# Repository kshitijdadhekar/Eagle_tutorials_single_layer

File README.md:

# Eagle_tutorials
The video tutorials can be found on <a href="https://www.youtube.com/watch?v=hYVQ5IdzsRg&list=PLr0mEvO7yBe6QHexsgU2WFUGesFFobGZp">Terminal Two's YouTube channel</a><br>

This repository contains the following:
1. Eagle schematic file
2. Eagle board file
3. BOM
4. Gerbers
5. PDFs of the schematic and the board files

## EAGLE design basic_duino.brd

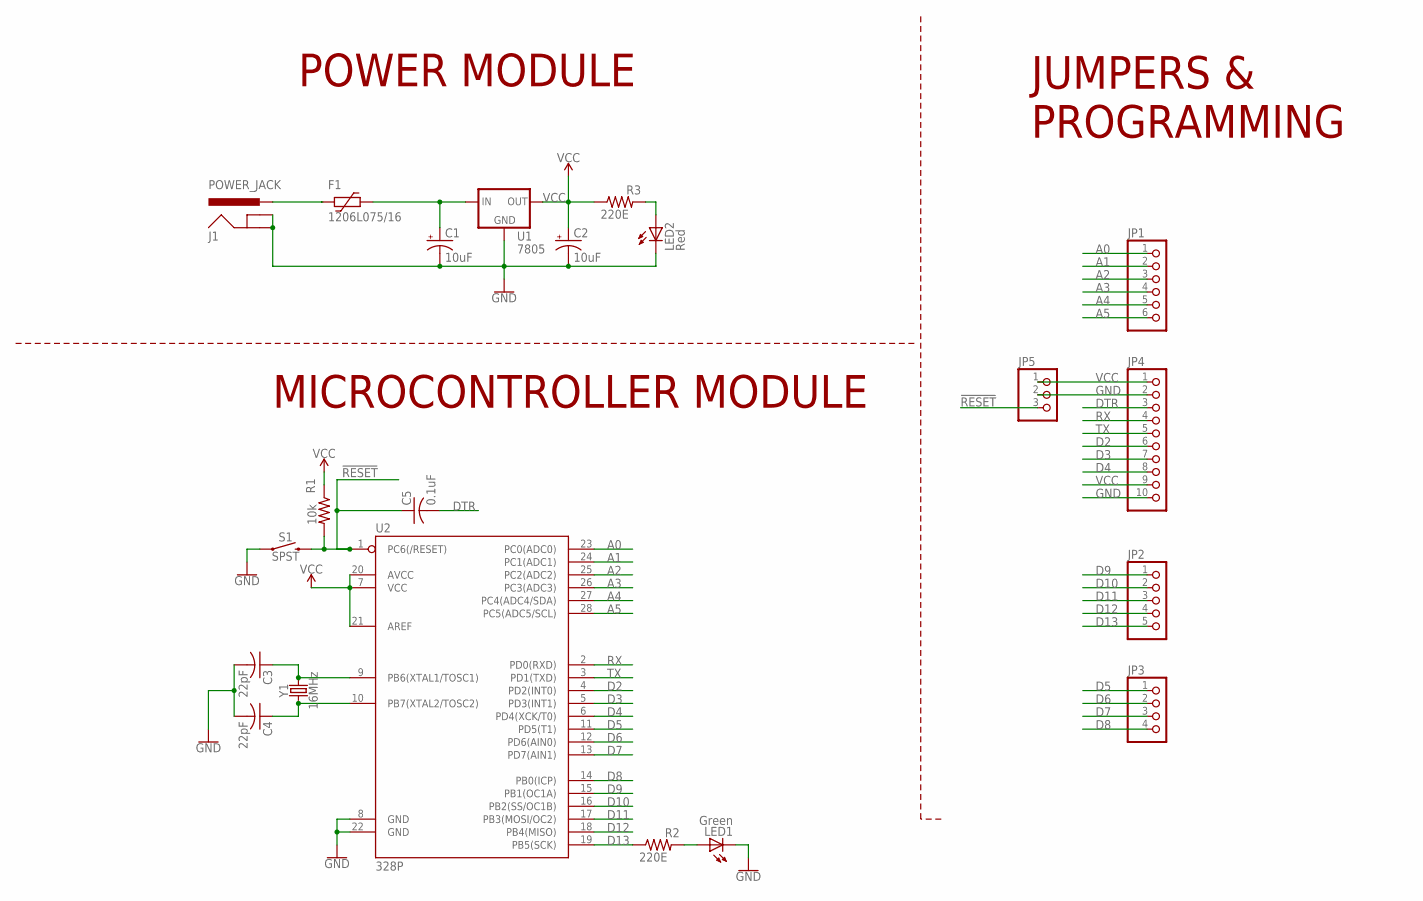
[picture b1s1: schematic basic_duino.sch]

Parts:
C1, C2: 10uF; E2,5-6
C3, C4: 22pF; C025-025X050
C5: 0.1uF; C025-025X050
F1: 1206L075/16; 1206L
J1: POWER_JACK; POWER_JACK_PTH
JP1: PINHD-1X6; 1X06
JP2: PINHD-1X5; 1X05
JP3: PINHD-1X4; 1X04
JP4: PINHD-1X10; 1X10
JP5: PINHD-1X3; 1X03
LED1: Green; LED3MM
LED2: Red; LED3MM
R1: 10k; 0204/7
R2, R3: 220E; 0204/7
S1: SPST; TACTILE_SWITCH_PTH_6.0MM
U1: 7805; 78XXS
U2: 328P; DIP28
Y1: 16MHz; HC49US

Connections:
!RESET: C5.1, JP5.3, R1.2, S1.3 (2), U2.1 (PC6(/RESET))
A0: JP1.1, U2.23 (PC0(ADC0))
A1: JP1.2, U2.24 (PC1(ADC1))
A2: JP1.3, U2.25 (PC2(ADC2))
A3: JP1.4, U2.26 (PC3(ADC3))
A4: JP1.5, U2.27 (PC4(ADC4/SDA))
A5: JP1.6, U2.28 (PC5(ADC5/SCL))
D2: JP4.6, U2.4 (PD2(INT0))
D3: JP4.7, U2.5 (PD3(INT1))
D4: JP4.8, U2.6 (PD4(XCK/T0))
D5: JP3.1, U2.11 (PD5(T1))
D6: JP3.2, U2.12 (PD6(AIN0))
D7: JP3.3, U2.13 (PD7(AIN1))
D8: JP3.4, U2.14 (PB0(ICP))
D9: JP2.1, U2.15 (PB1(OC1A))
D10: JP2.2, U2.16 (PB2(SS/OC1B))
D11: JP2.3, U2.17 (PB3(MOSI/OC2))
D12: JP2.4, U2.18 (PB4(MISO))
D13: JP2.5, R2.1, U2.19 (PB5(SCK))
DTR: C5.2, JP4.3
GND: C1.-, C2.-, C3.2, C4.2, J1.GND, J1.GNDBREAK, JP4.2, JP4.10, JP5.2, LED1.K (C), LED2.K (C), S1.1, U1.GND, U2.8 (GND), U2.22 (GND)
unnamed: C1.+, F1.1, U1.IN
unnamed: C3.1, U2.9 (PB6(XTAL1/TOSC1)), Y1.2
unnamed: C4.1, U2.10 (PB7(XTAL2/TOSC2)), Y1.1
unnamed: LED2.A, R3.2
unnamed: LED1.A, R2.2
unnamed: F1.2, J1.PWR
RX: JP4.4, U2.2 (PD0(RXD))
TX: JP4.5, U2.3 (PD1(TXD))
VCC: C2.+, JP4.1, JP4.9, JP5.1, R1.1, R3.1, U1.OUT, U2.7 (VCC), U2.20 (AVCC), U2.21 (AREF)

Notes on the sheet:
JUMPERS & PROGRAMMING
POWER MODULE
MICROCONTROLLER MODULE

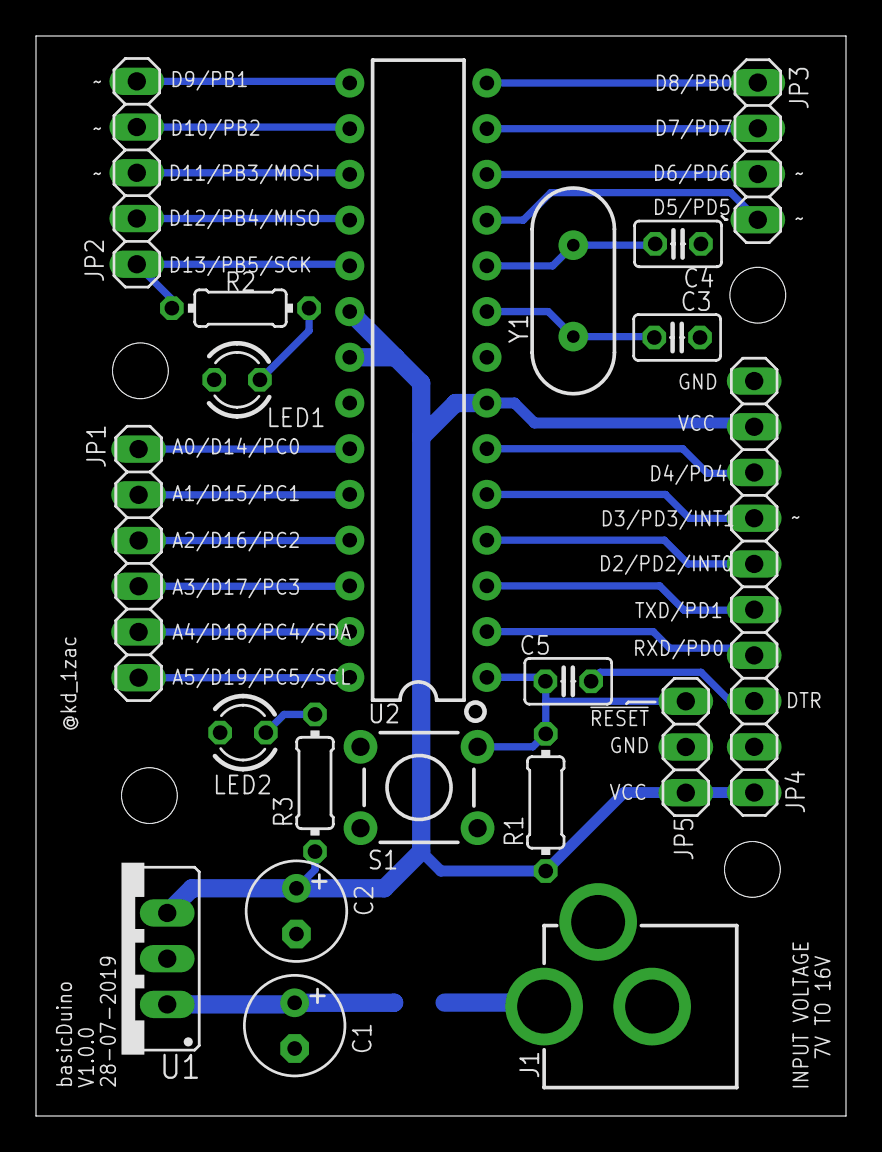
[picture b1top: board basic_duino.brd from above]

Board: 2 copper layers, 45.0 x 60.0 mm, 21 parts (1 on the bottom side), 30 nets.

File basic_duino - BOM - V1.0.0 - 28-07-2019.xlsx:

Qty | Value | Device | Package | Parts | Description | MPN
1 | 1206L075/16 | 1206L075/16 | 1206L | F1 | Polyfuse Resettable PTC | 1206L075/16
1 | 7805 | 78XXS | 78XXS | U1 | VOLTAGE REGULATOR
1 | 328P | ATMEGA328P_PDIP | DIP28 | U2 | Atmel 328P | ATMEGA328P-PU
2 | 10uF | CPOL-USE2.5-6 | E2,5-6 | C1, C2 | POLARIZED CAPACITOR, American symbol
1 | 16MHz | CRYSTAL-16MHZPTH-HC49US | HC49US | Y1 | 16MHz Crystal
1 | 0.1uF | C-US025-025X050 | C025-025X050 | C5 | CAPACITOR, American symbol
2 | 22pF | C-US025-025X050 | C025-025X050 | C3, C4 | CAPACITOR, American symbol
1 | Green | LED3MM | LED3MM | LED1 | LED
1 | Red | LED3MM | LED3MM | LED2 | LED
1 | SPST | MOMENTARY-SWITCH-SPST-PTH-6.0MM | TACTILE_SWITCH_PTH_6.0MM | S1 | Momentary Switch (Pushbutton) - SPST
1 |  | PINHD-1X10 | 1X10 | JP4 | PIN HEADER
1 |  | PINHD-1X3 | 1X03 | JP5 | PIN HEADER
1 |  | PINHD-1X4 | 1X04 | JP3 | PIN HEADER
1 |  | PINHD-1X5 | 1X05 | JP2 | PIN HEADER
1 |  | PINHD-1X6 | 1X06 | JP1 | PIN HEADER
1 | POWER_JACK | POWER_JACK | POWER_JACK_PTH | J1 | Power Jack Connector
1 | 10k | R-US_0204/7 | 0204/7 | R1 | RESISTOR, American symbol
2 | 220E | R-US_0204/7 | 0204/7 | R2, R3 | RESISTOR, American symbol

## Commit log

2019-10-18 initial-V1.0.0

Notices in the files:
parts and their libraries:
SparkFun-Connectors: Licensing: Creative Commons ShareAlike 4.0 International - https://creativecommons.org/licenses/by-sa/4.0
